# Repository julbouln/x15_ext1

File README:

Simple extension board for Beagleboard X15, eagle schematics and layout included.

Main purpose is to add an LVDS interface through video out and SN75LVDS83B chip and some GPIO and stuff on hackable pin headers. It uses only P18 Beagleboard X15 port and measure 55.88x43.18mm.

Pin headers includes : 
- 2 3V3, 5V, 12V with GND pins, 
- 8 single channel LVDS pins
- X15 power off pin 
- 14 GPIOS which should be used as I2C(1), SPI(1), PWM(2?) and UART(2?).

Included my DTS files (tested on linux 4.9.4 and 4.4.44) for an AUO B156XW04 V5 screen (GPIO4_7 as EN, EHRPWM2B as backlight), as well as a ruby script to convert from EDID hex file to "panel-timing" node.

To recompile DTB :
$ git clone https://github.com/RobertCNelson/dtb-rebuilder
$ cd dtb-rebuilder
$ cp ../x15_ext1/linux/am57xx-beagle-x15.dts src/arm
$ make src/arm/am57xx-beagle-x15.dtb

Unfortunately for 1366 width display, kernel need to be modified and recompiled.
Edit drivers/gpu/drm/omapdrm/dss/dpi.c then comment theses lines :
//   if (timings->x_res % 8 != 0)
//	return -EINVAL;
Not sure why there is this restriction since it seems to work without it.

Limitations and errata:
- only 18 bits single channel LVDS screens are supported
- LVDS positive pin 1 and LVDS positive pin 2 are inversed

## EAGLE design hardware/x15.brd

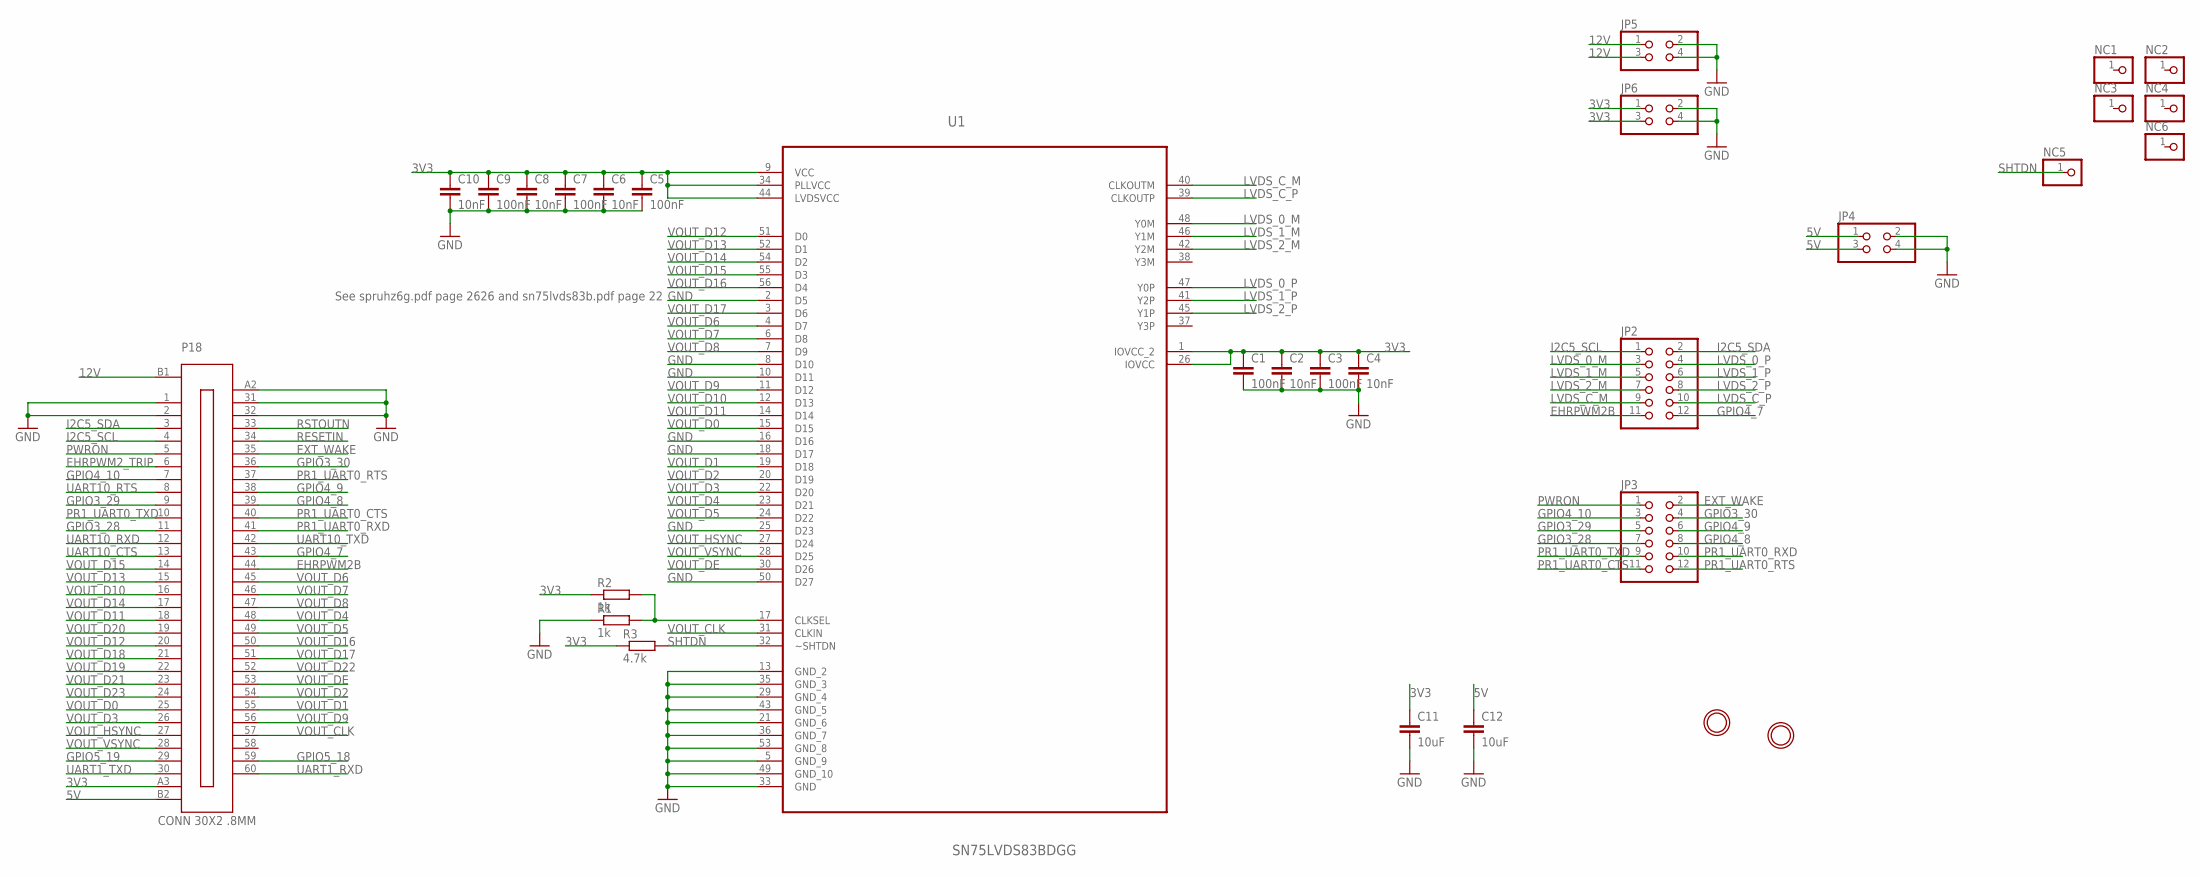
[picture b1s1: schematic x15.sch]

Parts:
C1, C3, C5, C7, C9: 100nF; C0603K
C2, C4, C6, C8, C10: 10nF; C0603K
C11, C12: 10uF; C1206K
JP2, JP3: PINHD-2X6; 2X06
JP4, JP5, JP6: PINHD-2X2; 2X02
NC1, NC2, NC3, NC4, NC5, NC6: PINHD-1X1; 1X01
P18: CONN 30X2 .8MM; CONN_FX18-60S-0.8SV15
R1, R2: 1k; R0603
R3: 4.7k; R0603
U1: SN75LVDS83BDGG; SOP50P810X120-56N
U$1, U$2: MOUNTINGHOLE2.5; MOUNTINGHOLE_2.5_PLATED

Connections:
3V3: C1.1, C2.1, C3.1, C4.1, C5.1, C6.1, C7.1, C8.1, C9.1, C10.1, C11.1, JP6.1, JP6.3, P18.A3, R2.1, R3.1, U1.1 (IOVCC_2), U1.9 (VCC), U1.26 (IOVCC), U1.34 (PLLVCC), U1.44 (LVDSVCC)
5V: C12.1, JP4.1, JP4.3, P18.B2
12V: JP5.1, JP5.3, P18.B1
EHRPWM2B: JP2.11, P18.44
EHRPWM2_TRIP: P18.6
EXT_WAKE: JP3.2, P18.35
GND: C1.2, C2.2, C3.2, C4.2, C5.2, C6.2, C7.2, C8.2, C9.2, C10.2, C11.2, C12.2, JP4.2, JP4.4, JP5.2, JP5.4, JP6.2, JP6.4, P18.1, P18.2, P18.31, P18.32, P18.A2, R1.1, U1.2 (D5), U1.5 (GND_9), U1.8 (D10), U1.10 (D11), U1.13 (GND_2), U1.16 (D16), U1.18 (D17), U1.21 (GND_6), U1.25 (D23), U1.29 (GND_4), U1.33 (GND), U1.35 (GND_3), U1.36 (GND_7), U1.43 (GND_5), U1.49 (GND_10), U1.50 (D27), U1.53 (GND_8)
GPIO3_28: JP3.7, P18.11
GPIO3_29: JP3.5, P18.9
GPIO3_30: JP3.4, P18.36
GPIO4_7: JP2.12, P18.43
GPIO4_8: JP3.8, P18.39
GPIO4_9: JP3.6, P18.38
GPIO4_10: JP3.3, P18.7
GPIO5_18: P18.59
GPIO5_19: P18.29
I2C5_SCL: JP2.1, P18.4
I2C5_SDA: JP2.2, P18.3
LVDS_0_M: JP2.3, U1.48 (Y0M)
LVDS_0_P: JP2.4, U1.47 (Y0P)
LVDS_1_M: JP2.5, U1.46 (Y1M)
LVDS_1_P: JP2.6, U1.41 (Y2P)
LVDS_2_M: JP2.7, U1.42 (Y2M)
LVDS_2_P: JP2.8, U1.45 (Y1P)
LVDS_C_M: JP2.9, U1.40 (CLKOUTM)
LVDS_C_P: JP2.10, U1.39 (CLKOUTP)
unnamed: R1.2, R2.2, U1.17 (CLKSEL)
PR1_UART0_CTS: JP3.11, P18.40
PR1_UART0_RTS: JP3.12, P18.37
PR1_UART0_RXD: JP3.10, P18.41
PR1_UART0_TXD: JP3.9, P18.10
PWRON: JP3.1, P18.5
RESETIN: P18.34
RSTOUTN: P18.33
SHTDN: NC5.1, R3.2, U1.32 (~SHTDN)
UART1_RXD: P18.60
UART1_TXD: P18.30
UART10_CTS: P18.13
UART10_RTS: P18.8
UART10_RXD: P18.12
UART10_TXD: P18.42
VOUT_CLK: P18.57, U1.31 (CLKIN)
VOUT_D0: P18.25, U1.15 (D15)
VOUT_D1: P18.55, U1.19 (D18)
VOUT_D2: P18.54, U1.20 (D19)
VOUT_D3: P18.26, U1.22 (D20)
VOUT_D4: P18.48, U1.23 (D21)
VOUT_D5: P18.49, U1.24 (D22)
VOUT_D6: P18.45, U1.4 (D7)
VOUT_D7: P18.46, U1.6 (D8)
VOUT_D8: P18.47, U1.7 (D9)
VOUT_D9: P18.56, U1.11 (D12)
VOUT_D10: P18.16, U1.12 (D13)
VOUT_D11: P18.18, U1.14 (D14)
VOUT_D12: P18.20, U1.51 (D0)
VOUT_D13: P18.15, U1.52 (D1)
VOUT_D14: P18.17, U1.54 (D2)
VOUT_D15: P18.14, U1.55 (D3)
VOUT_D16: P18.50, U1.56 (D4)
VOUT_D17: P18.51, U1.3 (D6)
VOUT_D18: P18.21
VOUT_D19: P18.22
VOUT_D20: P18.19
VOUT_D21: P18.23
VOUT_D22: P18.52
VOUT_D23: P18.24
VOUT_DE: P18.53, U1.30 (D26)
VOUT_HSYNC: P18.27, U1.27 (D24)
VOUT_VSYNC: P18.28, U1.28 (D25)

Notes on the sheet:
See spruhz6g.pdf page 2626 and sn75lvds83b.pdf page 22

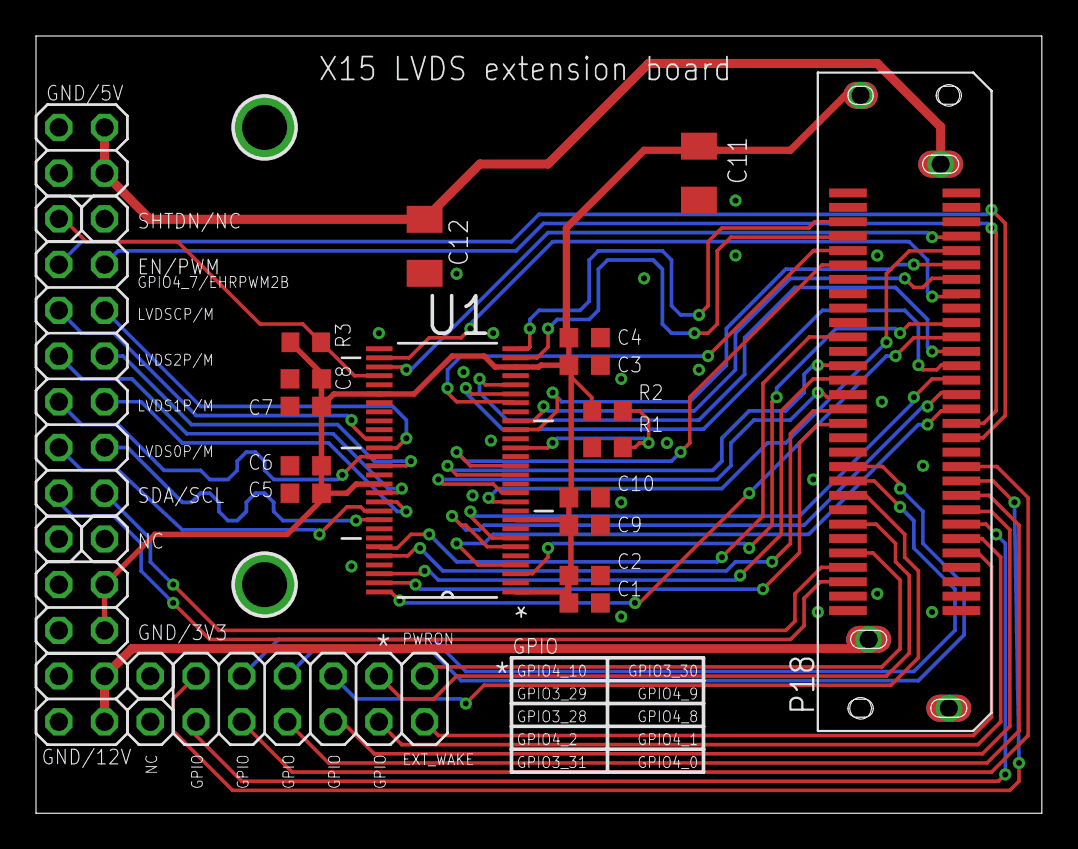
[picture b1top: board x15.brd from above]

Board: 2 copper layers, 55.9 x 43.2 mm, 30 parts (0 on the bottom side), 52 nets.

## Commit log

2017-01-28 4.4 dts + readme update

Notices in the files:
parts and their libraries:
microbuilder: This work is placed in the public domain, and may be freely used for commercial and non-commercial work with the following conditions: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
